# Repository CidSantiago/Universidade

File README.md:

Projects developed during Computer Engineering Course at UFC (Universidade Federal do Ceará).

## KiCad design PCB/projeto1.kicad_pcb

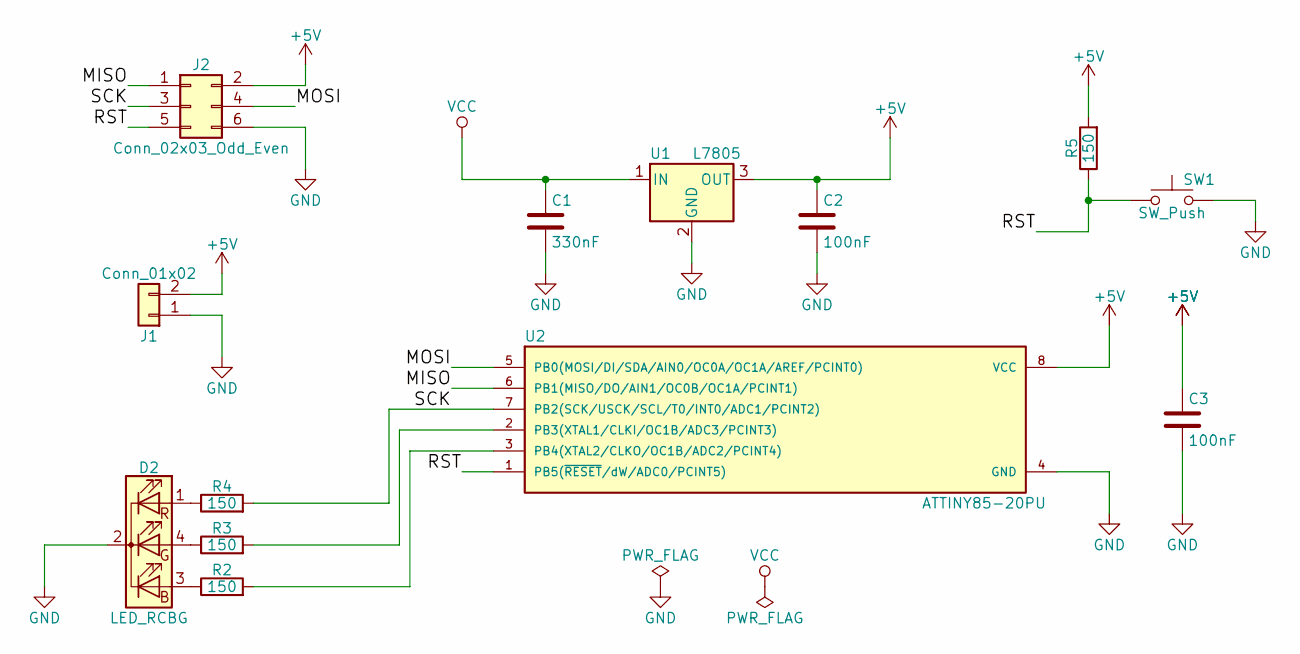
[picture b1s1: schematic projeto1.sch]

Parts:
C1: 330nF; C_Disc_D5.0mm_W2.5mm_P5.00mm
C2, C3: 100nF; C_Disc_D5.0mm_W2.5mm_P5.00mm
D2: LED_RCBG; LED-RGB-5MM_Common_Cathode
J1: Conn_01x02; Pin_Header_Straight_1x02_Pitch2.54mm
J2: Conn_02x03_Odd_Even; Pin_Header_Straight_2x03_Pitch2.54mm
R2, R3, R4, R5: 150; R_Axial_DIN0207_L6.3mm_D2.5mm_P7.62mm_Horizontal
SW1: SW_Push; SW_PUSH_6mm
U1: L7805; TO-220-3_Vertical
U2: ATTINY85-20PU; DIP-8_W7.62mm

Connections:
+5V: C2.1, C3.1, J1.2, J2.2, R5.2, U1.3 (OUT), U2.8 (VCC)
/MISO: J2.1, U2.6 (PB1(MISO/DO/AIN1/OC0B/OC1A/PCINT1))
/MOSI: J2.4, U2.5 (PB0(MOSI/DI/SDA/AIN0/OC0A/OC1A/AREF/PCI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)
/RST: J2.5, R5.1, SW1.1, U2.1 (PB5(~RESET~/dW/ADC0/PCINT5))
/SCK: J2.3, R4.2, U2.7 (PB2(SCK/USCK/SCL/T0/INT0/ADC1/PCINT2))
GND: C1.2, C2.2, C3.2, D2.2 (K), J1.1, J2.6, SW1.2, U1.2 (GND), U2.4 (GND)
unnamed: D2.1 (RA), R4.1
unnamed: D2.3 (BA), R2.1
unnamed: D2.4 (GA), R3.1
unnamed: R2.2, U2.3 (PB4(XTAL2/CLKO/OC1B/ADC2/PCINT4))
unnamed: R3.2, U2.2 (PB3(XTAL1/CLKI/OC1B/ADC3/PCINT3))
VCC: C1.1, U1.1 (IN)

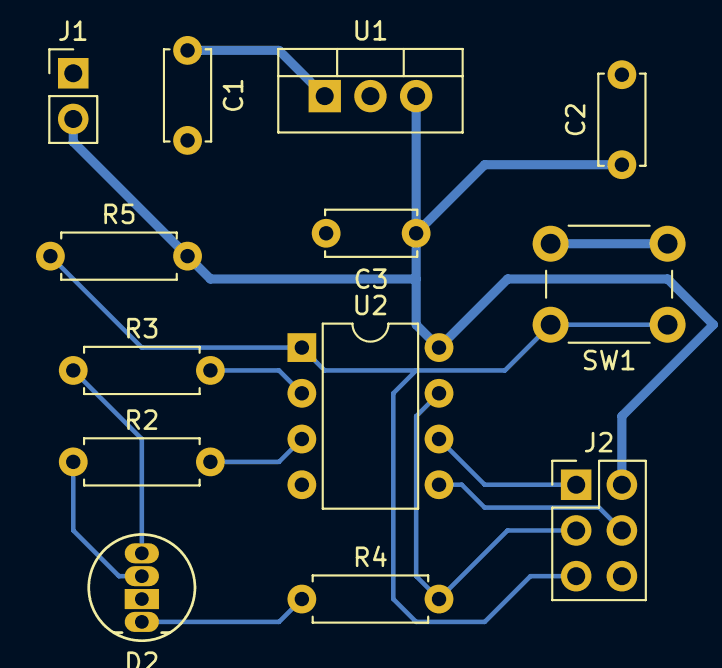
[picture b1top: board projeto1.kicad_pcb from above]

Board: 2 copper layers, 13 parts (0 on the bottom side), 12 nets.

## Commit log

2019-08-16 Analise e Desempenho
    Python codes to pre-process and analyze data.
2019-08-16 Introduction to control systems
    MATLAB codes
2019-08-16 Database fundamentals
    SQL Server and python codes
2019-08-16 Applied Computational intelligence
    R codes.
2019-08-16 Microcontrollers
    C codes using STM32cubeMX IDE
2019-08-16 Numeric Methods
    Python codes
2019-08-16 PCB
    Simple PCB development using KiCAD
2019-08-16 Digital Image Processing
    MATLAB codes
2019-08-16 Oriented Object Programming
    JAVA codes
2019-08-16 Computer Network
    Package Analysis using Wireshark
    Socket programming using python
    Network Topology using Cisco software
2019-08-16 Distributed Systems
    Python codes
2019-08-16 Embeed System
    Parking Sensor using a raspberry Pi. Python codes
2019-08-16 VHDL Summer Course
    VHDL codes
2019-09-11 Web Development First Exercise
    Development of the firsts pure htmls pages.
2019-09-11 WebDev 01 - Fixes
    Little adjustments in WebDev 01 pages
2019-09-16 WebDev 02
    Development of 2 stylesheets in CSS
2019-09-23 WebDev 03
    Start of development of exercise 03 (Ajax) and exercise 04 (EJS, Express) of Web Development course.
2019-09-30 WebDev 04
    Exercise 04 (Express, EJS) of Web Development course.
2019-10-16 Fix WebDev 04
    Minor fixes
2019-10-16 WebDev 05
    Layout EJS, Cookies
2019-10-29 WebDev 06 prep
    Reallocate imgs and jsons to better placement and access
2019-10-31 WebDev 06 (incomplete)
    Use of Multer and changing JSON datas
2019-11-04 WebDev 06
    Finish Multer exercise. Updating JSONs and Book images
2019-11-11 WebDev 07
    Added function to create new book and delete
2022-12-06 Bump qs, body-parser and express in /webDev
    Bumps [qs](https://github.com/ljharb/qs) to 6.11.0 and updates ancestor dependencies [qs](https://github.com/ljharb/qs), [body-parser](https://github.com/expressjs/body-parser) and [express](https://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
    Updates `qs` from 6.7.0 to 6.11.0
    - [Release notes](https://github.com/ljharb/qs/releases)
    - [Changelog](https://github.com/ljharb/qs/blob/main/CHANGELOG.md)
    - [Commits](https://github.com/ljharb/qs/compare/v6.7.0...v6.11.0)
    Updates `body-parser` from 1.19.0 to 1.20.1
2022-12-11 Bump express from 4.17.1 to 4.17.3 in /webDev
    Bumps [express](https://github.com/expressjs/express) from 4.17.1 to 4.17.3.
    - [Release notes](https://github.com/expressjs/express/releases)
    - [Changelog](https://github.com/expressjs/express/blob/master/History.md)
    - [Commits](https://github.com/expressjs/express/compare/4.17.1...4.17.3)
    ---
    updated-dependencies:
2023-03-03 Bump minimist and mkdirp in /webDev
    Bumps [minimist](https://github.com/minimistjs/minimist) and [mkdirp](https://github.com/isaacs/node-mkdirp). These dependencies needed to be updated together.
    Updates `minimist` from 0.0.8 to 1.2.8
    - [Release notes](https://github.com/minimistjs/minimist/releases)
    - [Changelog](https://github.com/minimistjs/minimist/blob/main/CHANGELOG.md)
    - [Commits](https://github.com/minimistjs/minimist/compare/v0.0.8...v1.2.8)
    Updates `mkdirp` from 0.5.1 to 0.5.6
